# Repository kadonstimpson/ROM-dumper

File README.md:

# ROM‑Dumper for STM32F072 Discovery  
University of Utah • Embedded Systems Project

## Team Members
Cubby DeBry,  
Joshua Elieson,  
Kadon Stimpson,  
Yunzu Hou  

---

## Table of Contents
1. [About the Project](#about-the-project)  
2. [Hardware](#hardware)  
   * [Discovery‑board Modifications](#discovery-board-modifications)  
3. [Software](#software)  
   * [Supported Cartridge Types](#supported-cartridge-types)  
   * [Dumping Options](#dumping-options)  
4. [Getting Started](#getting-started)  
5. [Usage](#usage)  
6. [Roadmap / To‑Do](#roadmap--to-do)  

---

## About the Project
This project implements a **stand‑alone cartridge dumper** that interfaces classic Nintendo hand‑held game cards with an STM32F072 Discovery board.  
* **Hardware**—custom daughter‑board hosting the game‑card connector, level‑shifters and SD‑card slot.  
* **Firmware**—bank‑aware bus driver plus USB‑CDC and FatFS back‑ends.  
* **Host Tools**—minimal Python/Tk GUI for one‑click dumps on macOS, Windows, and Linux.

All design files live under `Hardware/`; Desktop tools reside in `Tools/`.

---

## Hardware
Design iteration **v1** is complete and electrically validated.  SD‑card and game‑card buses have been verified on real cartridges.

### Discovery‑board Modifications
The stock STM32F072 Discovery must be tweaked to expose additional GPIO lines:
| Component | Action |
|-----------|--------|
| C26, C27, C28 | **Remove** |
| R38, R39, R40 | **Remove** |
| SBx (solder bridges on rear) | **Bridge** matching removed caps/resistors |

> **Orientation tip**: the Discovery board plugs into the daughter‑board with its **USB‑Mini port facing the SD‑card slot**. No directional silk is present, so double‑check before powering.

---

## Software
### Supported Cartridge Types
| System | Status | Notes |
|--------|--------|-------|
| **Game Boy / Game Boy Color** |  | |
| &nbsp;&nbsp;No MBC | ✔ Implemented *(untested)*  |                                       |
| &nbsp;&nbsp;MBC1 | ✔ Implemented *(untested)*    |                                       |
| &nbsp;&nbsp;MBC2 | ✔ Implemented *(untested)*    |                                       |
| &nbsp;&nbsp;MBC3 | ✔ Implemented *(untested)*    | Pokemon, etc.                         |
| &nbsp;&nbsp;MBC5 | ✔ Implemented & **tested**    | Almost all later games                |
| &nbsp;&nbsp;MBC6 | ✔ Implemented *(untested)*    |                                       |
| &nbsp;&nbsp;MBC7 | ✔ Implemented *(untested)*    |                                       |
| &nbsp;&nbsp;Other/rare MBCs                      | ✖ Not yet | Handful of known games    |
| **Game Boy Advance** | ✔ Full dumps (32 MiB assumed) |                                   |

### Dumping Options
* **USB‑CDC** – streams data over 1 Mbaud VCP; proven with GBA cartridges.  
* **SD‑Card** – direct‐to‑FAT file dumps; already linked into MBC5 flow, pending integration for other types.

---

## Getting Started
```bash
# clone repository
git clone https://github.com/your‑org/ROM‑dumper.git
cd ROM‑dumper

# create virtual environment for host tools
python3 -m venv .venv
source .venv/bin/activate

# build firmware (requires arm‑gcc & stm32cubemx)
pio run -t upload
```

---

## Usage
### Stand‑alone (SD‑Card)
1. Insert a FAT formatted SD card.  
2. Power the board via USB. 
3. Insert cartridge
6. Press *Reset* button 
7. Retrieve `.gba`/`.gbc`/`.gb` file from SD.

### USB‑CDC
1. Power the board via USB. 
2. Run `dumperGUI.py`.
3. Select corresponding serial port from list.
4. Provide file name for dump output (including `.gba`/`.gbc`/`.gb`).
5. Press *Start Dump* button 
6. Retrieve `.gba`/`.gbc`/`.gb` file

---

## Roadmap / To‑Do
* **Mode selector**—hardware or menu to choose SD vs USB without a PC.  
* **DMA + double buffering** for both back‑ends to maximise throughput.  
* **GBA ROM trimming**—detect true ROM size to avoid 32 MiB paddings.  
* **Integrate SD flow** into all MBC drivers.
* **V2 Hardware** standalone dumper with lcd and onboard STM32.  
* **Automated self‑test** jig for production.

---

© 2025 University of Utah Embedded Systems Group • Licensed under MIT (see `LICENSE`).

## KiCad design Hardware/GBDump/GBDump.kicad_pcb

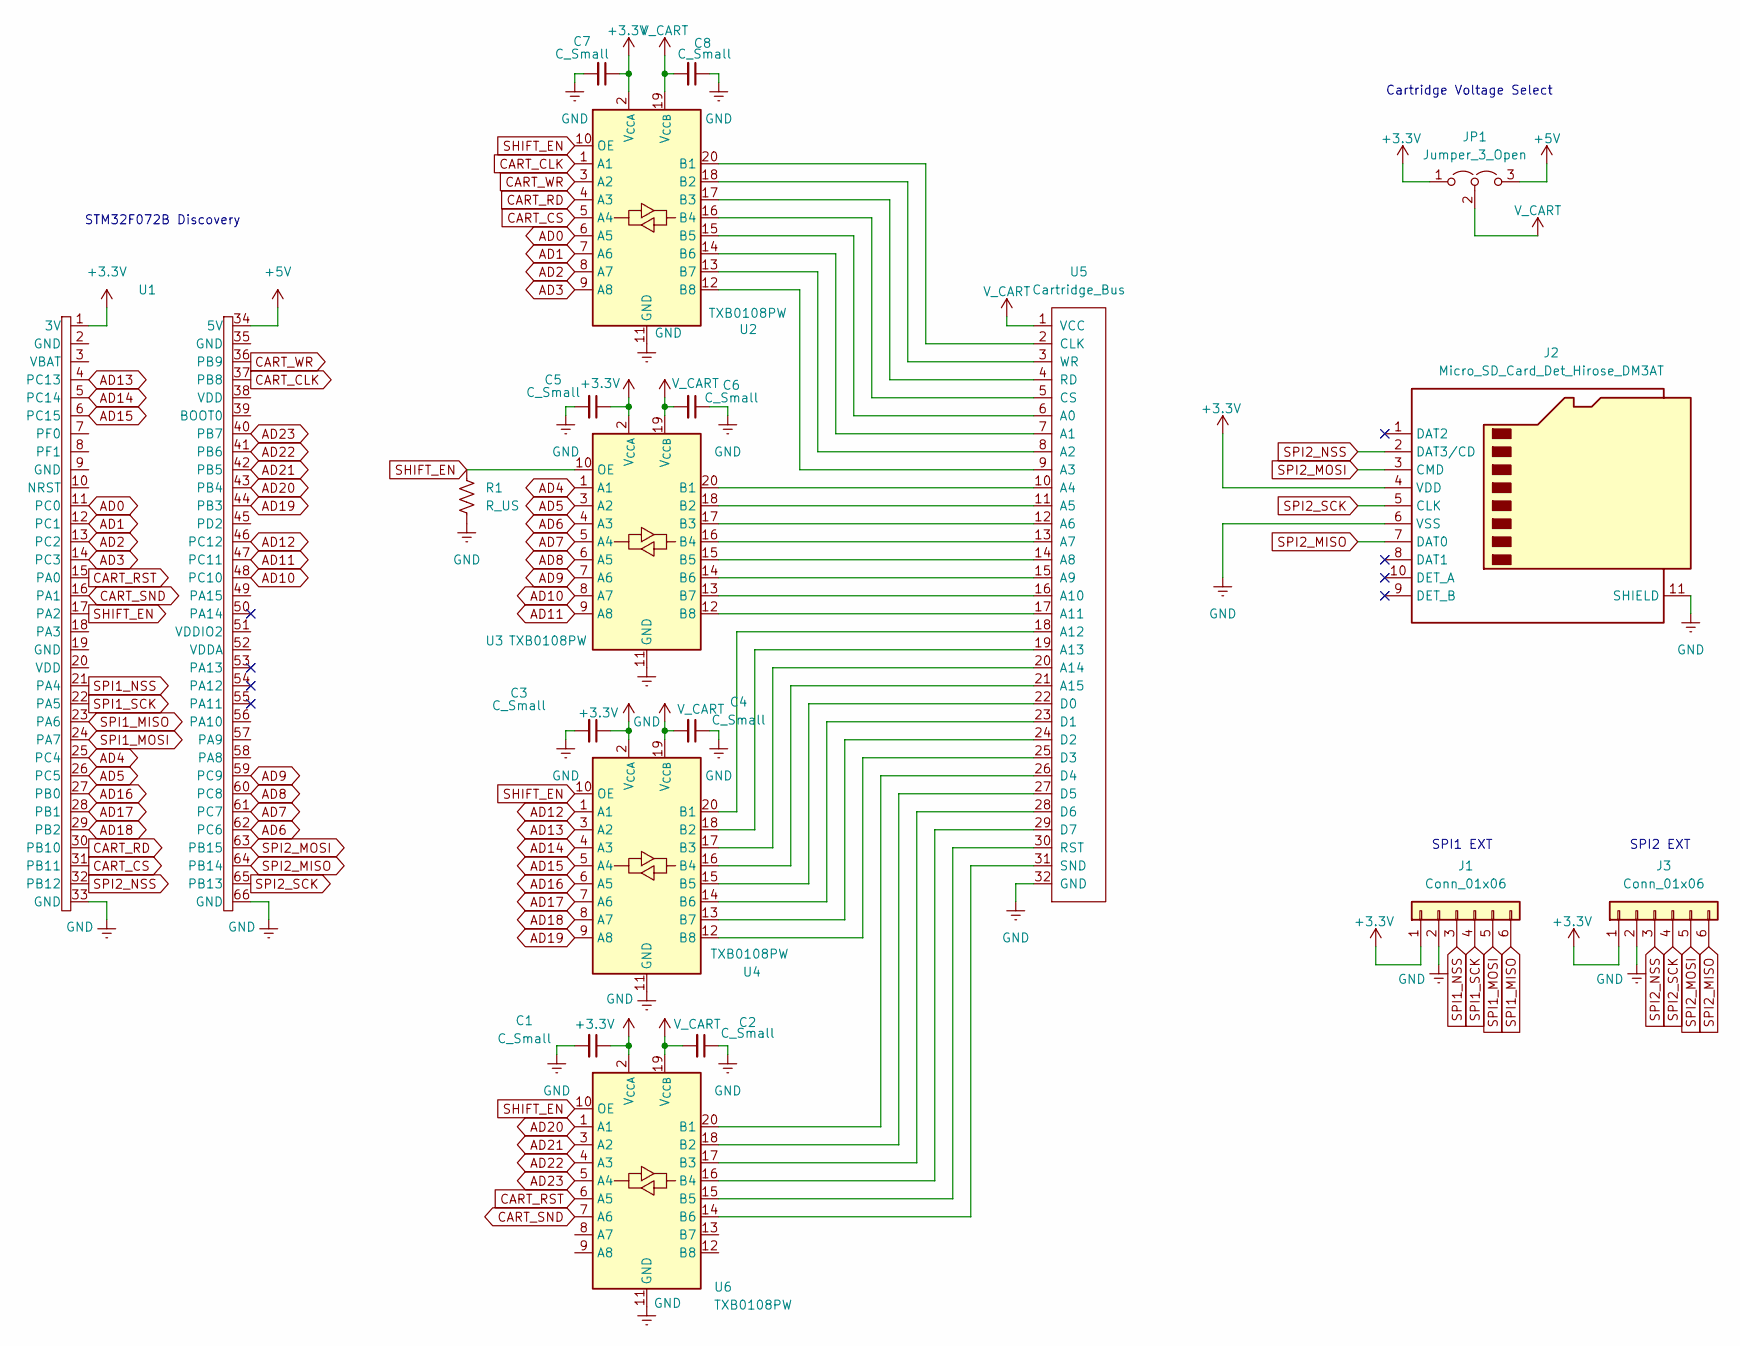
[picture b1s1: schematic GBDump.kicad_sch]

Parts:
C1, C2, C3, C4, C5, C6, C7, C8: C_Small; C_1206_3216Metric
J1, J3: Conn_01x06; PinHeader_1x06_P2.54mm_Vertical
J2: Micro_SD_Card_Det_Hirose_DM3AT; microSD_HC_Hirose_DM3AT-SF-PEJM5
JP1: Jumper_3_Open; PinHeader_1x03_P2.54mm_Vertical
R1: R_US; R_1206_3216Metric
U1: STM32F072B-DISCO
U2, U3, U4, U6: TXB0108PW; TSSOP-20_4.4x6.5mm_P0.65mm
U5: Cartridge_Bus; Game_Boy_Advance_Edge_Connector

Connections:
+3.3V: C1.1, C3.1, C5.1, C7.1, J1.1, J2.4 (VDD), J3.1, JP1.1 (A), U1.1 (3V), U2.2 (V_{CCA}), U3.2 (V_{CCA}), U4.2 (V_{CCA}), U6.2 (V_{CCA})
+5V: JP1.3 (B), U1.34 (5V)
AD0: U1.11 (PC0), U2.6 (A5)
AD1: U1.12 (PC1), U2.7 (A6)
AD2: U1.13 (PC2), U2.8 (A7)
AD3: U1.14 (PC3), U2.9 (A8)
AD4: U1.25 (PC4), U3.1 (A1)
AD5: U1.26 (PC5), U3.3 (A2)
AD6: U1.62 (PC6), U3.4 (A3)
AD7: U1.61 (PC7), U3.5 (A4)
AD8: U1.60 (PC8), U3.6 (A5)
AD9: U1.59 (PC9), U3.7 (A6)
AD10: U1.48 (PC10), U3.8 (A7)
AD11: U1.47 (PC11), U3.9 (A8)
AD12: U1.46 (PC12), U4.1 (A1)
AD13: U1.4 (PC13), U4.3 (A2)
AD14: U1.5 (PC14), U4.4 (A3)
AD15: U1.6 (PC15), U4.5 (A4)
AD16: U1.27 (PB0), U4.6 (A5)
AD17: U1.28 (PB1), U4.7 (A6)
AD18: U1.29 (PB2), U4.8 (A7)
AD19: U1.44 (PB3), U4.9 (A8)
AD20: U1.43 (PB4), U6.1 (A1)
AD21: U1.42 (PB5), U6.3 (A2)
AD22: U1.41 (PB6), U6.4 (A3)
AD23: U1.40 (PB7), U6.5 (A4)
CART_CLK: U1.37 (PB8), U2.1 (A1)
CART_CS: U1.31 (PB11), U2.5 (A4)
CART_RD: U1.30 (PB10), U2.4 (A3)
CART_RST: U1.15 (PA0), U6.6 (A5)
CART_SND: U1.16 (PA1), U6.7 (A6)
CART_WR: U1.36 (PB9), U2.3 (A2)
GND: C1.2, C2.1, C3.2, C4.1, C5.2, C6.1, C7.2, C8.1, J1.2, J2.6 (VSS), J2.11 (SHIELD), J3.2, R1.2, U1.33 (GND), U1.66 (GND), U2.11 (GND), U3.11 (GND), U4.11 (GND), U5.32 (GND), U6.11 (GND)
unnamed: U2.20 (B1), U5.2 (CLK~)
unnamed: U2.18 (B2), U5.3 (WR)
unnamed: U2.17 (B3), U5.4 (RD)
unnamed: U2.16 (B4), U5.5 (CS)
unnamed: U2.15 (B5), U5.6 (A0)
unnamed: U2.14 (B6), U5.7 (A1)
unnamed: U2.13 (B7), U5.8 (A2)
unnamed: U2.12 (B8), U5.9 (A3)
unnamed: U3.20 (B1), U5.10 (A4)
unnamed: U3.18 (B2), U5.11 (A5)
unnamed: U3.17 (B3), U5.12 (A6)
unnamed: U3.16 (B4), U5.13 (A7)
unnamed: U3.15 (B5), U5.14 (A8)
unnamed: U3.14 (B6), U5.15 (A9)
unnamed: U3.13 (B7), U5.16 (A10)
unnamed: U3.12 (B8), U5.17 (A11)
unnamed: U4.20 (B1), U5.18 (A12)
unnamed: U4.18 (B2), U5.19 (A13)
unnamed: U4.17 (B3), U5.20 (A14)
unnamed: U4.16 (B4), U5.21 (A15)
unnamed: U4.15 (B5), U5.22 (D0)
unnamed: U4.14 (B6), U5.23 (D1)
unnamed: U4.13 (B7), U5.24 (D2)
unnamed: U4.12 (B8), U5.25 (D3)
unnamed: U5.26 (D4), U6.20 (B1)
unnamed: U5.27 (D5), U6.18 (B2)
unnamed: U5.28 (D6), U6.17 (B3)
unnamed: U5.29 (D7), U6.16 (B4)
unnamed: U5.30 (RST), U6.15 (B5)
unnamed: U5.31 (SND), U6.14 (B6)
SHIFT_EN: R1.1, U1.17 (PA2), U2.10 (OE), U3.10 (OE), U4.10 (OE), U6.10 (OE)
SPI1_MISO: J1.6, U1.23 (PA6)
SPI1_MOSI: J1.5, U1.24 (PA7)
SPI1_NSS: J1.3, U1.21 (PA4)
SPI1_SCK: J1.4, U1.22 (PA5)
SPI2_MISO: J2.7 (DAT0), J3.6, U1.64 (PB14)
SPI2_MOSI: J2.3 (CMD), J3.5, U1.63 (PB15)
SPI2_NSS: J2.2 (DAT3/CD), J3.3, U1.32 (PB12)
SPI2_SCK: J2.5 (CLK), J3.4, U1.65 (PB13)
V_CART: C2.2, C4.2, C6.2, C8.2, JP1.2 (C), U2.19 (V_{CCB}), U3.19 (V_{CCB}), U4.19 (V_{CCB}), U5.1 (VCC), U6.19 (V_{CCB})

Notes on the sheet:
Cartridge Voltage Select
STM32F072B Discovery
SPI1 EXT
SPI2 EXT

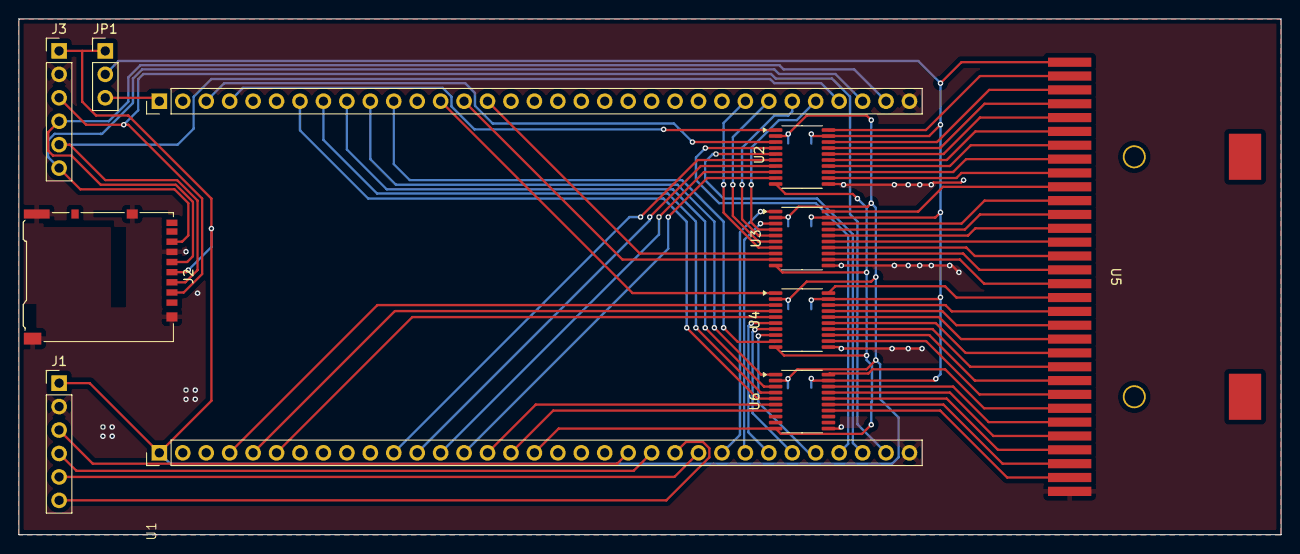
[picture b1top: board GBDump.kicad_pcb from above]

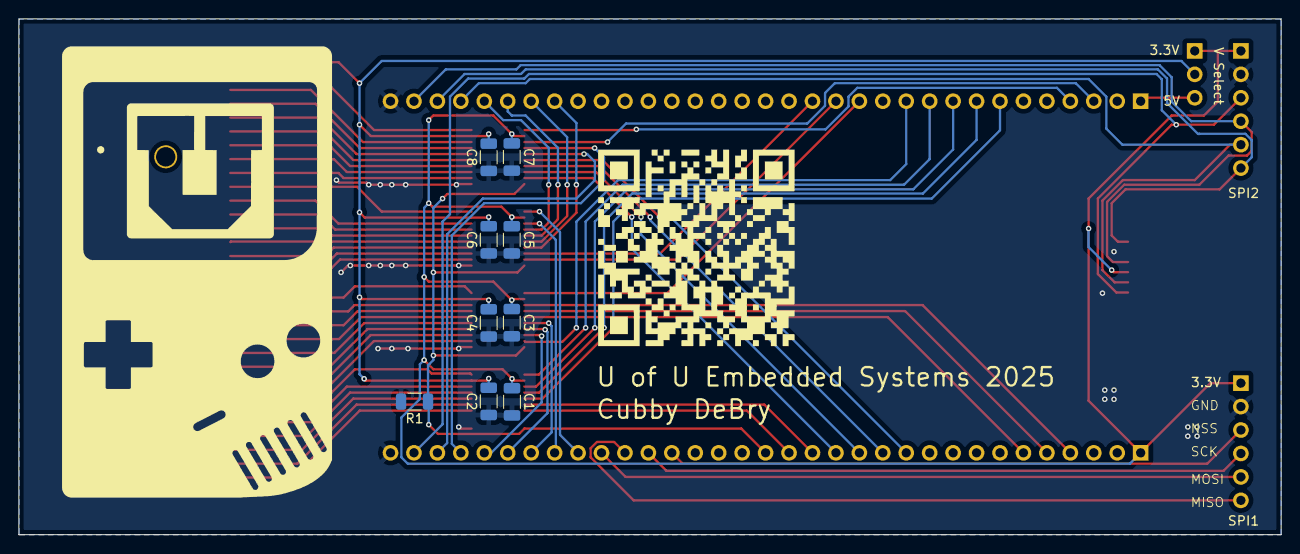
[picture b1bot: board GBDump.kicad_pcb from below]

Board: 2 copper layers, 136.8 x 55.9 mm, 19 parts (9 on the bottom side), 73 nets.

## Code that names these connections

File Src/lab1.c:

#include "stm32f0xx_hal.h"
#include <string.h>
#include <stdio.h>
#include "gameboy.h"

#define DATA_PORT GPIOC
#define ADDR_LOW_PORT GPIOC   // PC0-PC15
#define ADDR_HIGH_PORT GPIOB  // PB0-PB7
#define CART_RD_PORT GPIOB
#define CART_RD_PIN GPIO_PIN_10

void GPIO_Init_All(void);
void GPIO_UART1_Init(void);
void UART1_Init(void);
void set_address(uint16_t addr);
uint8_t read_data_byte(void);
void send_serial(const char* msg);

int lab1_main(void) {
    HAL_Init();
    // SystemClock_Config();

    __HAL_RCC_GPIOA_CLK_ENABLE();  // Enable GPIOA clock
    __HAL_RCC_GPIOB_CLK_ENABLE();
    __HAL_RCC_GPIOC_CLK_ENABLE();

    GPIO_UART1_Init();  
    UART1_Init();  
    
    GPIO_InitTypeDef RDWR = {0};  // Upper address bus
    RDWR.Pin = GPIO_PIN_0 | GPIO_PIN_9 | GPIO_PIN_10;
    RDWR.Mode = GPIO_MODE_OUTPUT_PP;  // Push-pull output
    RDWR.Pull = GPIO_NOPULL;
    RDWR.Speed = GPIO_SPEED_FREQ_LOW;

    HAL_GPIO_Init(GPIOB, &RDWR);

    shift_enable();

    HAL_GPIO_WritePin(GPIOB, GPIO_PIN_10, GPIO_PIN_SET);    // Read disable
    HAL_GPIO_WritePin(GPIOB, GPIO_PIN_9, GPIO_PIN_SET);     // Write disable

    HAL_GPIO_WritePin(GPIOB, GPIO_PIN_0, GPIO_PIN_RESET);    // Reset cart
    HAL_Delay(10);
    HAL_GPIO_WritePin(GPIOB, GPIO_PIN_0, GPIO_PIN_SET);
    HAL_Delay(10);

    // test_bank_switch();

    char buf[16];

    GBC_read_bank(0x0000);

    while(1){}

    // for (uint16_t addr = 0x100; addr <= 0x14F; addr++) {
    //     set_address(addr);

    //     HAL_GPIO_WritePin(CART_RD_PORT, CART_RD_PIN, GPIO_PIN_RESET);
    //     HAL_Delay(1);

    //     GPIO_InitTypeDef GPIO_InitStruct = {0};
    //     GPIO_InitStruct.Pin = 0x00FF; // PC0-PC7
    //     GPIO_InitStruct.Mode = GPIO_MODE_INPUT;
    //     HAL_GPIO_Init(DATA_PORT, &GPIO_InitStruct);

    //     uint8_t data = read_data_byte();

    //     HAL_GPIO_WritePin(CART_RD_PORT, CART_RD_PIN, GPIO_PIN_SET);

    //     sprintf(msg, "Addr 0x%04X: 0x%02X\r\n", addr, data);
    //     send_serial(msg);
    //     HAL_Delay(10);
    // }

    // while (1) {
        // HAL_Delay(100);
        // printf("\nUSART Test...");
    // }
}

void GPIO_Init_All(void) {
    __HAL_RCC_GPIOB_CLK_ENABLE();
    __HAL_RCC_GPIOC_CLK_ENABLE();

    // Address bus (PC0-PC15 + PB0-PB7)
    GPIO_InitTypeDef GPIO_InitStruct = {0};
    GPIO_InitStruct.Pin = 0xFFFF;
    GPIO_InitStruct.Mode = GPIO_MODE_OUTPUT_PP;
    HAL_GPIO_Init(GPIOC, &GPIO_InitStruct);

    GPIO_InitStruct.Pin = 0x00FF;
    HAL_GPIO_Init(GPIOB, &GPIO_InitStruct);

    // CART_RD
    GPIO_InitStruct.Pin = CART_RD_PIN;
    HAL_GPIO_Init(CART_RD_PORT, &GPIO_InitStruct);
}

void set_address(uint16_t addr) {
    // 写入 PC0-PC15
    for (int i = 0; i < 16; i++) {
        HAL_GPIO_WritePin(GPIOC, (1 << i), (addr & (1 << i)) ? GPIO_PIN_SET : GPIO_PIN_RESET);
    }
}

uint8_t read_data_byte(void) {
    uint8_t value = 0;
    for (int i = 0; i < 8; i++) {
        value |= (HAL_GPIO_ReadPin(DATA_PORT, (1 << i)) << i);
    }
    return value;
}

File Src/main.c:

#include "stm32f0xx_hal.h"
#include <string.h>
#include <stdio.h>
#include "GBC.h"
#include "GBA.h"
#include "sd.h"
#include "main.h"
#include "uart.h"
#include "usb_device.h"
#include "usbd_cdc_if.h"

volatile uint32_t last_isr;

void Init_All(void);
static void Gyro_SPI2_Init();
static void USB_ClockEnable();

FATFS fs;

int main(void) {
  Init_All();   // Add any additional initialization here

  // initialize sd card
  // disk_initialize(0);
  // try to mount sd card
  FRESULT res = f_mount(&fs, "", 1);

  if (res != FR_OK)
  {
    printf("f_mount result = %d\r\n", res);
  }

  // GBA_test();   // Test GBA stuff here

  // GBC_test();
  GBA_test();
  // sd_cmd_test();
  // sd_test();

  f_unmount("");
  // sd_test();

  while(1){
    CDC_Transmit_FS((uint8_t *)"Hello, host!\\r\\n", 14);
  }
}

void Init_All(){
  HAL_Init();
  SystemClock_Config();
  USB_ClockEnable();

  __HAL_RCC_GPIOA_CLK_ENABLE();  // Enable GPIOA clock
  __HAL_RCC_GPIOB_CLK_ENABLE();
  __HAL_RCC_GPIOC_CLK_ENABLE();

  __HAL_RCC_PWR_CLK_ENABLE();   // Enable USB clock and power
  MX_USB_DEVICE_Init();      // Hangs, removed temporarily
 
  HAL_PWR_EnableBkUpAccess(); // Enable access to backup domain

  RCC->BDCR &= ~RCC_BDCR_LSEON; // Disable LSE oscillator to free PC14 and PC15

  while (RCC->BDCR & RCC_BDCR_LSERDY) {}  // Wait until LSE is fully disabled

  Gyro_SPI2_Init();
  GPIO_UART1_Init();  
  UART1_Init(); 
  MX_RTC_Init();
  rtc_check_and_set();

  setvbuf(stdout, NULL, _IONBF, 0); // make printf unbuffered 

  GPIO_InitTypeDef RDWR = {0};  // Upper address bus
  RDWR.Pin = GPIO_PIN_9 | GPIO_PIN_10 | GPIO_PIN_11;
  RDWR.Mode = GPIO_MODE_OUTPUT_PP;  // Push-pull output
  RDWR.Pull = GPIO_NOPULL;
  RDWR.Speed = GPIO_SPEED_FREQ_LOW;

  GPIO_InitTypeDef RST = {0};  // Cart Reset
  RST.Pin = GPIO_PIN_0;
  RST.Mode = GPIO_MODE_OUTPUT_PP;  // Push-pull output
  RST.Pull = GPIO_NOPULL;
  RST.Speed = GPIO_SPEED_FREQ_LOW;
  
  HAL_GPIO_Init(GPIOB, &RDWR);
  HAL_GPIO_Init(GPIOA, &RST);

  shift_enable();

  HAL_GPIO_WritePin(GPIOB, GPIO_PIN_10, GPIO_PIN_SET);      // Read disable
  HAL_GPIO_WritePin(GPIOB, GPIO_PIN_9, GPIO_PIN_SET);       // Write disable
  // HAL_GPIO_WritePin(GPIOB, GPIO_PIN_11, GPIO_PIN_RESET);    // Pull /CS low

  HAL_GPIO_WritePin(GPIOA, GPIO_PIN_0, GPIO_PIN_RESET);     // Reset cart
  HAL_Delay(10);
  HAL_GPIO_WritePin(GPIOA, GPIO_PIN_0, GPIO_PIN_SET);
  HAL_Delay(10);
}

static void Gyro_SPI2_Init(void)  // set gyro pins to high impedence
{
    __HAL_RCC_GPIOB_CLK_ENABLE();
    __HAL_RCC_SPI2_CLK_ENABLE();

    GPIO_InitTypeDef g = {0};

    g.Pin       = GPIO_PIN_13 | GPIO_PIN_14 | GPIO_PIN_15;  // PB13 - SCK, PB14 - MISO, PB15 - MOSI
    g.Mode      = GPIO_MODE_AF_PP;
    g.Pull      = GPIO_NOPULL;
    g.Speed     = GPIO_SPEED_FREQ_HIGH;
    g.Alternate = GPIO_AF0_SPI2;
    HAL_GPIO_Init(GPIOB, &g);

    __HAL_RCC_GPIOC_CLK_ENABLE(); // PC0 - CS
    g.Pin   = GPIO_PIN_0;
    g.Mode  = GPIO_MODE_OUTPUT_PP;
    g.Speed = GPIO_SPEED_FREQ_HIGH;
    HAL_GPIO_Init(GPIOC, &g);
    HAL_GPIO_WritePin(GPIOC, GPIO_PIN_0, GPIO_PIN_SET);  // CS high

    static SPI_HandleTypeDef h;
    h.Instance               = SPI2;
    h.Init.Mode              = SPI_MODE_MASTER;
    h.Init.Direction         = SPI_DIRECTION_2LINES;
    h.Init.DataSize          = SPI_DATASIZE_8BIT;
    h.Init.CLKPolarity       = SPI_POLARITY_LOW;
    h.Init.CLKPhase          = SPI_PHASE_1EDGE;
    h.Init.NSS               = SPI_NSS_SOFT;
    h.Init.BaudRatePrescaler = SPI_BAUDRATEPRESCALER_256;
    h.Init.FirstBit          = SPI_FIRSTBIT_MSB;
    HAL_SPI_Init(&h);

    uint8_t wr[2];

    /* 1. Power‑down the device (CTRL_REG1, addr 0x20) */
    wr[0] = 0x20;               // address, MSB=0 → write
    wr[1] = 0x00;               // PD=0, ODR=00 => power‑down
    HAL_GPIO_WritePin(GPIOC, GPIO_PIN_0, GPIO_PIN_RESET);
    HAL_SPI_Transmit(&h, wr, 2, HAL_MAX_DELAY);
    HAL_GPIO_WritePin(GPIOC, GPIO_PIN_0, GPIO_PIN_SET);

    /* 2. Disable every interrupt on both pins (CTRL_REG3, addr 0x22) */
    wr[0] = 0x22;
    wr[1] = 0x10;               // all I2_/I1_ high impedence
    HAL_GPIO_WritePin(GPIOC, GPIO_PIN_0, GPIO_PIN_RESET);
    HAL_SPI_Transmit(&h, wr, 2, HAL_MAX_DELAY);
    HAL_GPIO_WritePin(GPIOC, GPIO_PIN_0, GPIO_PIN_SET);
}

static void USB_ClockEnable(void){
  __HAL_RCC_HSI48_ENABLE();
  while(!__HAL_RCC_GET_FLAG(RCC_FLAG_HSI48RDY));

  __HAL_RCC_USB_CONFIG(RCC_USBCLKSOURCE_HSI48);
  __HAL_RCC_CRS_CLK_ENABLE();
  __HAL_RCC_USB_CLK_ENABLE();
}

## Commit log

2025-03-21 Added name to README for checkpoint 0.
2025-03-31 Started schematic, made STMDiscovery symbol, added TXB0108 level shifters.
2025-03-31 Finished address and data bus, level shifting power and ground, jumper for voltage selection.
2025-03-31 Added SPI header, symbol files
2025-04-04 Added symbol files.
2025-04-04 Added PDF version of schematic
2025-04-05 Added SD interface and level shift enable pin with pull down
2025-04-05 Fixed CART_VCC label
2025-04-05 Finished board layout and routing, will add silkscreen.
2025-04-05 PCB finished other than silkscreen.
2025-04-05 Finished silkscreen, generated gerbers.
2025-04-09 Serial monitor
2025-04-10 Added some config to platformio.ini and USART2 initialization function for USB debug.
2025-04-10 Finished UART2 initialization. Added UART test message.
2025-04-11 Removed UART2 functions.
2025-04-15 Added functions I've been testing on a different board in gameboy.c, move uart and initialization to uart.c
2025-04-15 Moved UART functions.
2025-04-16 Updated Gameboy.c
2025-04-16 Fixed build errors
2025-04-16 added discovery board datasheets
2025-04-16 initial work on sd card
2025-04-16 Restructured using main. Split gameboy into GBC and GBA.
2025-04-16 Finalized restructuring, updated main.
2025-04-19 A few minor bug fixes, fixed /RST pin.
2025-04-19 Fixed bank switching and printf, working on MBC5 handler.
2025-04-19 Implemented full MBC5 dump function. Tested working with 5 games.
2025-04-19 Added preliminary GBA functions. Worked out issue overwriting all of GPIOB making RD and CS to drop causing high impedence state. Reading semi-legible data, cart name appears scrambled.
2025-04-20 Tweaked test dump, added byte swap, initial cs toggle to clear cart. First working GBA dump.
2025-04-20 Changed GBA loop from byte address to word address.
2025-04-20 Tried blocking to increase speeds, UART is topping out maybe USB CDC faster. Need to add functions to query rom header and handle dump.
2025-04-20 Added STMCube files for usb cdc, updated platformio.ini
2025-04-21 Added USB CDC initializations and included new directiories in platformio.ini
2025-04-21 Added USB trasmit to GBA test function, untested.
2025-04-21 USB Init hangs, removed temporarily.
2025-04-21 Added MBC1 dump function. Still looking for games to test with. Bank switch function was intended for MBC5 and SHOULD still work for other switching. If having problems check that first.
2025-04-21 Fixed naming issue. Implemented MBC2 and MBC1.
2025-04-21 Fixed naming issue. Fixed wrong call in switch for MBC1.
2025-04-21 Okay bank switching methods are waaaay more diverse. Implemented much more comprehensive bank switcher (maybe 98% of games?). Again, need to find carts to test.
2025-04-21 Added separate MBC2 function.
2025-04-21 Added MBC3 function, mostly the same as 1 and 2.
2025-04-21 Added MBC6 and MBC7. GBC functionality pretty much finished.
2025-04-22 Fixed USB cdc initialization errors.
2025-04-22 Simple python gui, includes dropdown, text entry, button
2025-04-22 fixed spacing
2025-04-22 data writes to file, TODO: write COM dump to 'data'
2025-04-22 left TODO comments
2025-04-23 working write to sd card
2025-04-23 fixed printfs
2025-04-23 added implementation for com port dump
2025-04-23 Updated GBA.c
2025-04-23 allowing for custom port, updated baud rate
2025-04-23 updated dumper, should work
2025-04-23 work on sd write
2025-04-23 fixed filename
2025-04-25 changed all dumps to use buffered writes
2025-04-25 updated to use global buffer
2025-04-25 updated MBC reads to single function
2025-04-25 fixed typo in case statement
2025-04-25 update GBA.c from main
2025-04-25 updated spacing
2025-04-25 Cleaned up GBA.c, decided to stick with default 32MiB dumping for now, worry about cleaning and end detection later.
2025-04-25 Added helper functions to query available serial ports and add to list. Tweaked UI to allow for longer com port names.
2025-04-25 Tweaked GBA to wait for open serial port.
2025-04-25 Updated readme, moved Python GUI to /Tools
2025-04-25 Added simple handshake to GUI, fixed missed bytes in GBA.
2025-04-25 renamed file pointer
2025-04-25 work on GBA writes
2025-04-25 Tweaked GBA to wait for open serial port. Added host handshake to gui. Fixed missing bytes from GBA dumps.
2025-04-25 added old dump_MBC5 as backup
2025-04-26 Added demo video (small, needed to be < 100MB)
